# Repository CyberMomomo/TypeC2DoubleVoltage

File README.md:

# TypeC2DoubleVoltage
>
> ## Introduction
>
> This device is used for converting voltage from 5V input by USB Type-C Plug to any positive and negetive voltages from 1.25V to 30V.

> ## How to use
>
> Use the gerber files and bom from releases you could get a demo board which can produce +12V 40mA and -12V 40mA output. By changing R7, R8, R11, R14 you could get any other voltages you want. But you should use proper capacitors when you use the device to get other voltages in order to avoid the overvoltage. And any sigle volatge output should not load over 500mW or the output ripple will surge and the MC34063 may overheat.

> ## Performance
>
> For the demo board, the output ripple is lower than 1mVpp in unloaded test, and it is lower than 2mVpp when loading a 40mA output.

> ## Images
>
> 
> 
> 
>

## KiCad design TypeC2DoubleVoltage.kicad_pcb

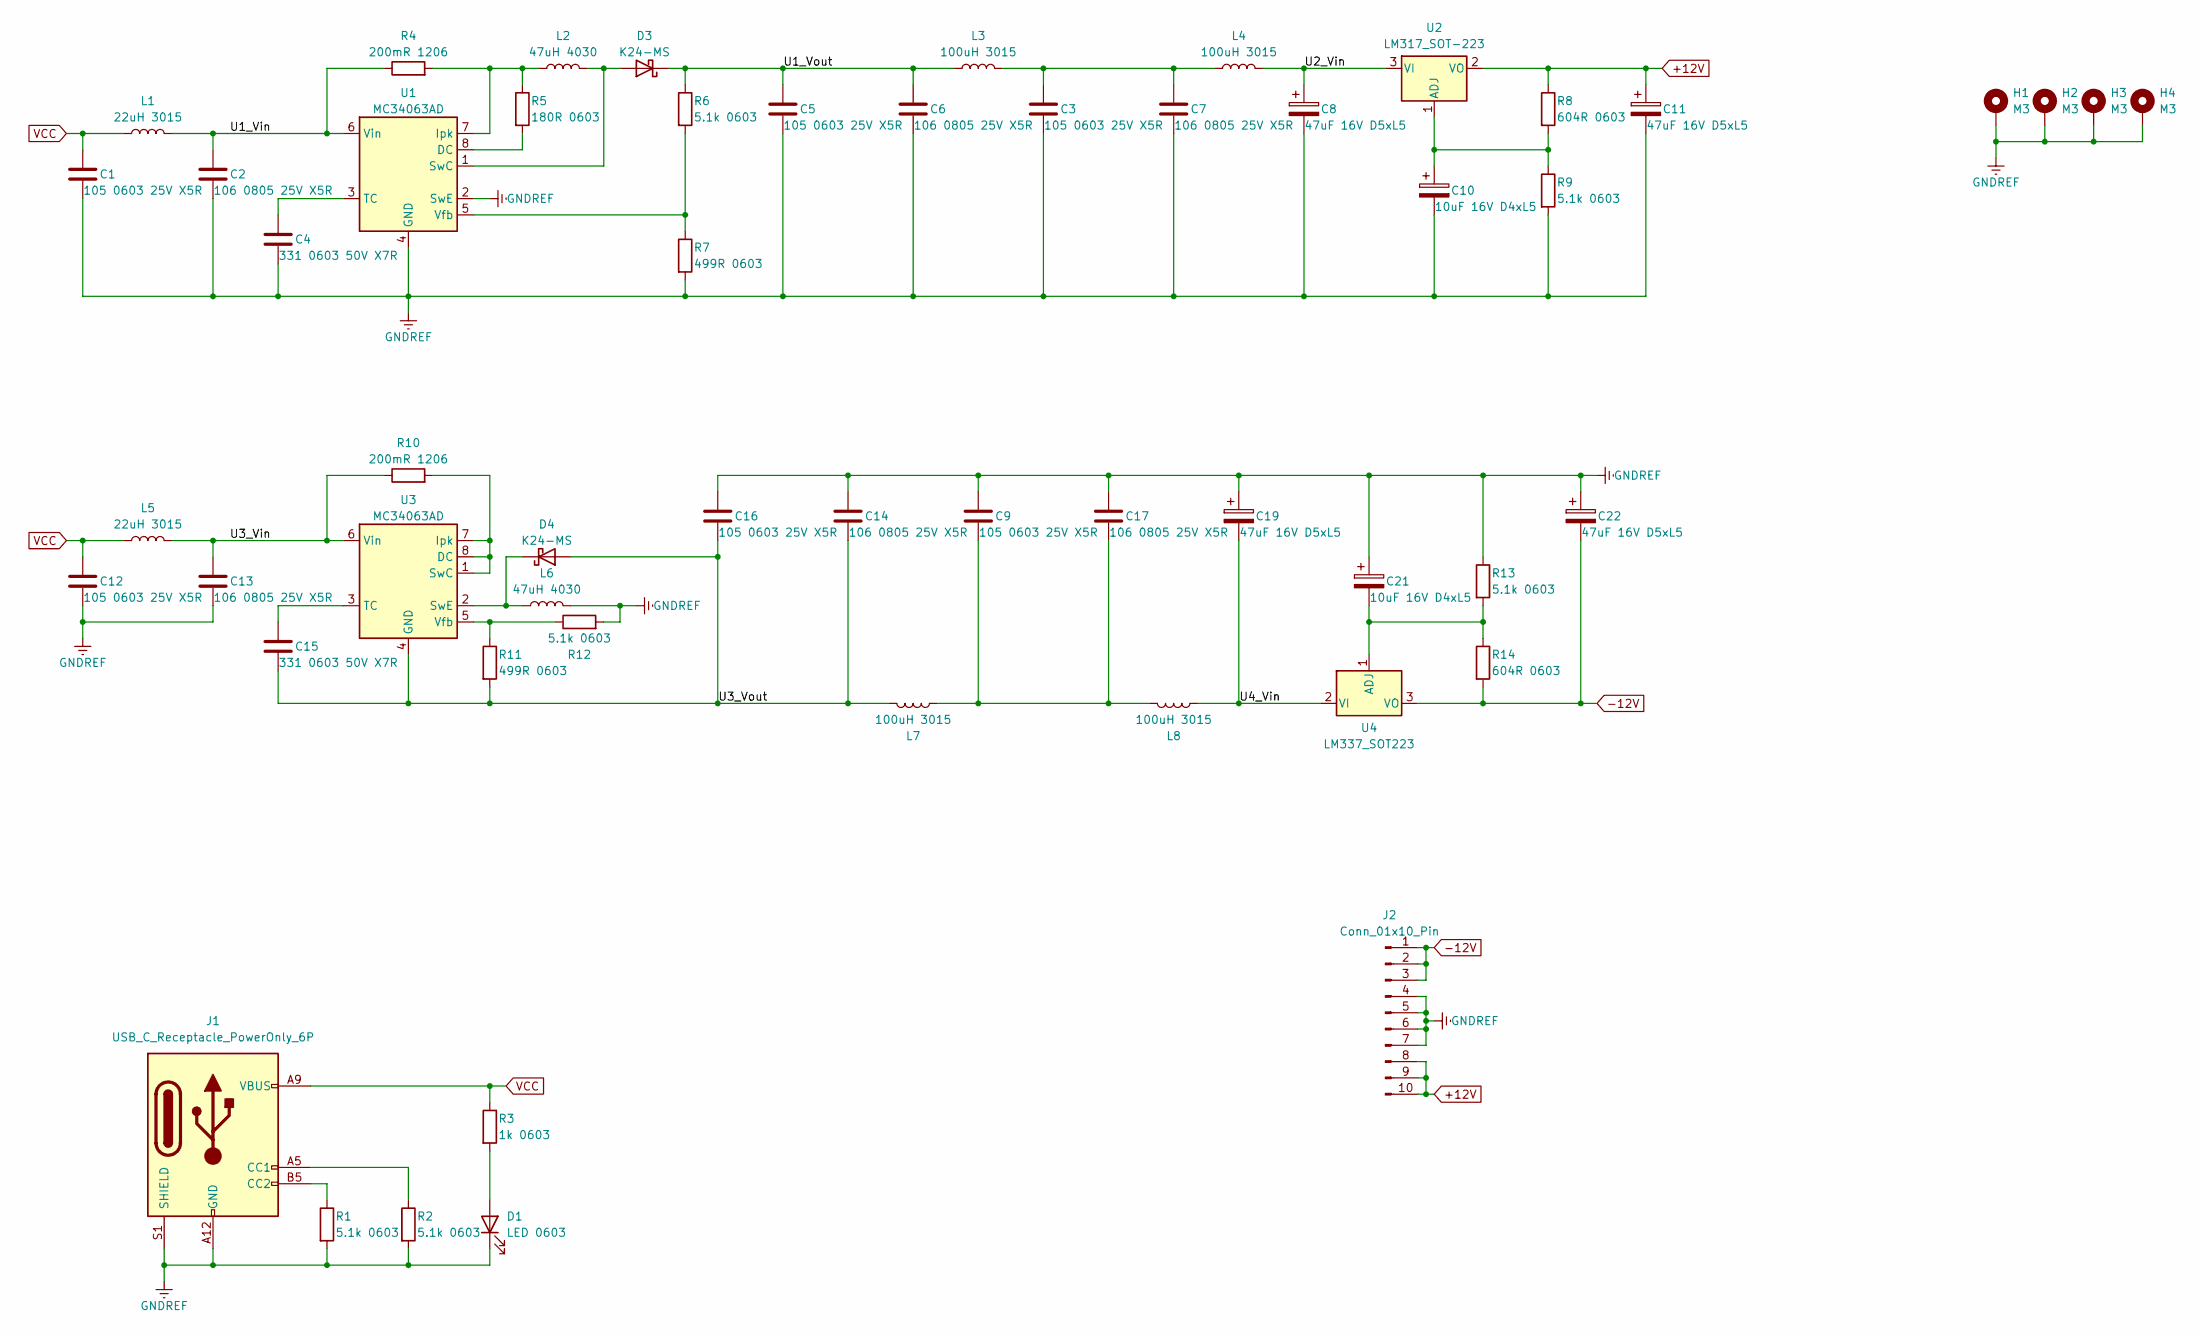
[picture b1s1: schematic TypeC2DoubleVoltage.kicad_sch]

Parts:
C1, C3, C5, C9, C12, C16: 105 0603 25V X5R; C_0603_1608Metric
C2, C6, C7, C13, C14, C17: 106 0805 25V X5R; C_0805_2012Metric
C4, C15: 331 0603 50V X7R; C_0603_1608Metric
C8, C11, C19, C22: 47uF 16V D5xL5; CP_Radial_D5.0mm_P2.00mm
C10, C21: 10uF 16V D4xL5; CP_Radial_D4.0mm_P1.50mm
D1: LED 0603; LED_0603_1608Metric
D3, D4: K24-MS; D_SOD-123F
H1, H2, H3, H4: M3; MountingHole_3.2mm_M3_Pad
J1: USB_C_Receptacle_PowerOnly_6P; USB_C_Receptacle_6P_01
J2: Conn_01x10_Pin; PinHeader_1x10_P2.54mm_Vertical
L1, L5: 22uH 3015; L_Changjiang_FNR3015S
L2, L6: 47uH 4030; L_Changjiang_FNR4030S
L3, L4, L7, L8: 100uH 3015; L_Changjiang_FNR3015S
R1, R2, R6, R9, R12, R13: 5.1k 0603; R_0603_1608Metric
R3: 1k 0603; R_0603_1608Metric
R4, R10: 200mR 1206; R_1206_3216Metric
R5: 180R 0603; R_0603_1608Metric
R7, R11: 499R 0603; R_0603_1608Metric
R8, R14: 604R 0603; R_0603_1608Metric
U1, U3: MC34063AD; SOIC-8_3.9x4.9mm_P1.27mm
U2: LM317_SOT-223; SOT-223-3_TabPin2
U4: LM337_SOT223; SOT-223-3_TabPin2

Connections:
+12V: C11.1, J2.8, J2.9, J2.10, R8.1, U2.2 (VO)
-12V: C22.2, J2.1, J2.2, J2.3, R14.2, U4.3 (VO)
/U1_Vin: C2.2, L1.2, R4.1, U1.6 (Vin)
/U1_Vout: C5.2, C6.2, D3.1 (K), L3.1, R6.1
/U2_Vin: C8.1, L4.2, U2.3 (VI)
/U3_Vin: C13.2, L5.2, R10.1, U3.6 (Vin)
/U3_Vout: C14.1, C15.1, C16.1, D4.2 (A), L7.1, R11.2, U3.4 (GND)
/U4_Vin: C19.2, L8.2, U4.2 (VI)
GNDREF: C1.1, C2.1, C3.1, C4.1, C5.1, C6.1, C7.1, C8.2, C9.2, C10.2, C11.2, C12.1, C13.1, C14.2, C16.2, C17.2, C19.1, C21.1, C22.1, D1.1 (K), H1.1, H2.1, H3.1, H4.1, J1.A12 (GND), J1.B12 (GND), J1.S1 (SHIELD), J2.4, J2.5, J2.6, J2.7, L6.2, R1.2, R2.2, R7.2, R9.2, R12.2, R13.1, U1.2 (SwE), U1.4 (GND)
unnamed: C3.2, C7.2, L3.2, L4.1
unnamed: C9.1, C17.1, L7.2, L8.1
unnamed: D1.2 (A), R3.2
unnamed: D3.2 (A), L2.2, U1.1 (SwC)
unnamed: D4.1 (K), L6.1, U3.2 (SwE)
unnamed: J1.A5 (CC1), R2.1
unnamed: J1.B5 (CC2), R1.1
unnamed: R5.2, U1.8 (DC)
unnamed: L2.1, R4.2, R5.1, U1.7 (Ipk)
unnamed: C4.2, U1.3 (TC)
unnamed: R6.2, R7.1, U1.5 (Vfb)
unnamed: C10.1, R8.2, R9.1, U2.1 (ADJ)
unnamed: R10.2, U3.1 (SwC), U3.7 (Ipk), U3.8 (DC)
unnamed: C15.2, U3.3 (TC)
unnamed: R11.1, R12.1, U3.5 (Vfb)
unnamed: C21.2, R13.2, R14.1, U4.1 (ADJ)
VCC: C1.2, C12.2, J1.A9 (VBUS), J1.B9 (VBUS), L1.1, L5.1, R3.1

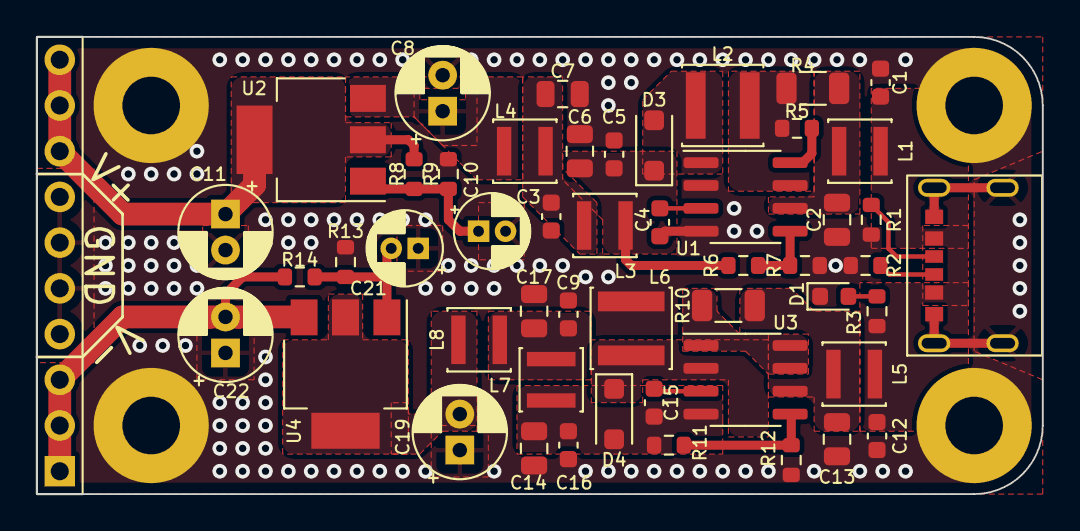
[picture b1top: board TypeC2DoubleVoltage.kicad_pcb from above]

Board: 2 copper layers, 55.9 x 25.4 mm, 55 parts (0 on the bottom side), 26 nets.

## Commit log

2024-02-06 Create Project
2024-02-06 Almost Finish
2024-03-20 Add images
